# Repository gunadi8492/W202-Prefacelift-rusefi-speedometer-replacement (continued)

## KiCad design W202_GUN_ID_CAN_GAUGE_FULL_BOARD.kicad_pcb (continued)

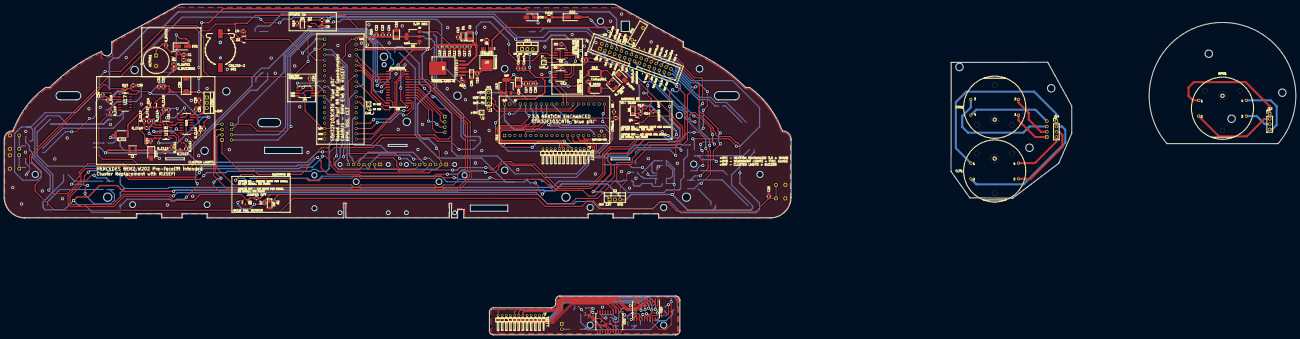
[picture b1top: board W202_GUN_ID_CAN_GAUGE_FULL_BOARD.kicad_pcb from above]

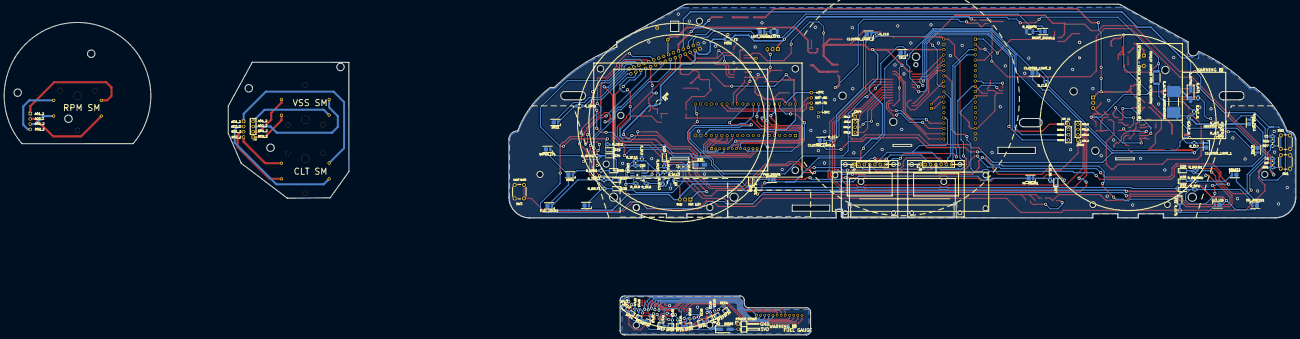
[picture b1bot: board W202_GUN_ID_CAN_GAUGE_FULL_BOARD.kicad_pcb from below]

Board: 2 copper layers, 380.0 x 103.2 mm, 236 parts (112 on the bottom side), 177 nets.

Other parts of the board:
+5VC: PinHeader_1x02_P2.00mm_Vertical
CAN_J: PinHeader_1x02_P2.00mm_Vertical
CAN_J#2: PinHeader_1x02_P2.00mm_Vertical
DIODE: 1N4007; D_SMA_Handsoldering
F3, F3#2: Polyfuse; Fuse_1206_3216Metric_Pad1.42x1.75mm_HandSolder
IGN12V JUMPER FOR ALTERNATOR: 10; R_2512_6332Metric
J3#2: VSS; PinHeader_1x04_P2.54mm_Vertical
JUMPER OPT: R_0805_2012Metric
JUMPER OPT#2: R_0805_2012Metric
POWER POINT: PinHeader_1x02_P2.54mm_Horizontal
R_WL8: 47K; R_0805_2012Metric

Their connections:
+5C: +5VC.2; also elsewhere on the board
+5VD: DIODE.1 (K), R_WL8.1; also elsewhere on the board
+5VD_S: DIODE.2 (A), POWER POINT.2
AO1_1: J3#2.1; also elsewhere on the board
AO2_1: J3#2.2; also elsewhere on the board
BO1_1: J3#2.3; also elsewhere on the board
BO2_1: J3#2.4; also elsewhere on the board
BULB_SNSR: JUMPER OPT.2; also elsewhere on the board
GND: +5VC.1, POWER POINT.1; also elsewhere on the board
HI_BEAM: JUMPER OPT#2.1; also elsewhere on the board
unnamed 69: JUMPER OPT.1; also elsewhere on the board
unnamed 70: JUMPER OPT#2.2; also elsewhere on the board
unnamed 104: R_WL8.2; also elsewhere on the board
RX CAN: CAN_J.1, CAN_J#2.1; also elsewhere on the board
TX CAN: CAN_J.2, CAN_J#2.2; also elsewhere on the board

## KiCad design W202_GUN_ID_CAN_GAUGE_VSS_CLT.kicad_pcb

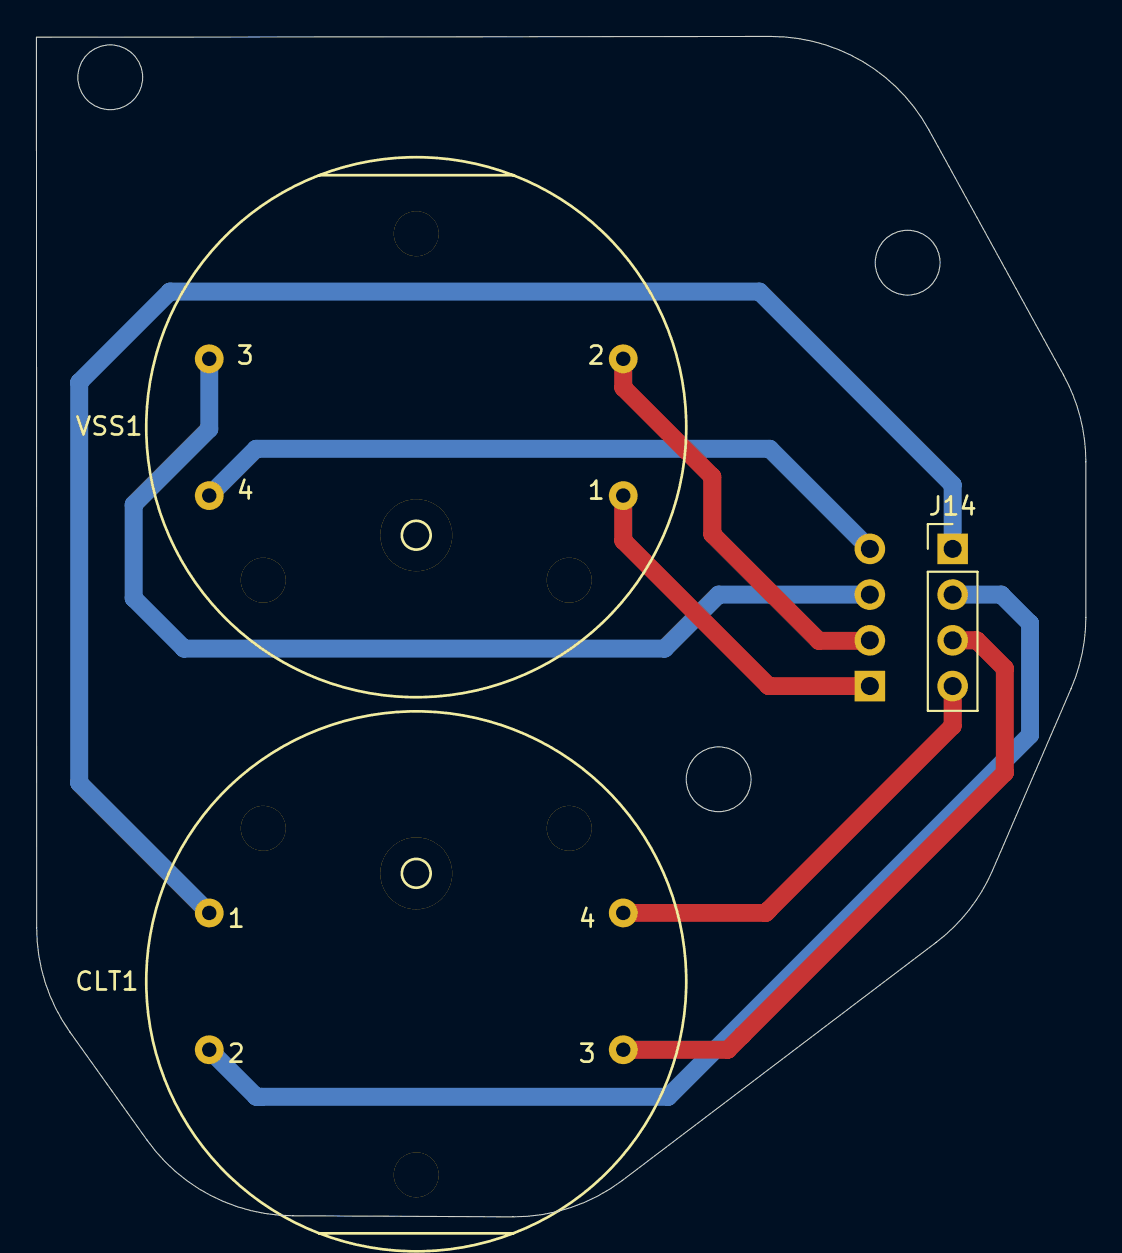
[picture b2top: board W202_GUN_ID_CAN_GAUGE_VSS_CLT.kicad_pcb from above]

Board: 2 copper layers, 58.3 x 65.6 mm, 4 parts (1 on the bottom side), 8 nets.

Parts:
CLT1: SM; X27-168__V2
J3: VSS; PinHeader_1x04_P2.54mm_Vertical
J14: CLT; PinHeader_1x04_P2.54mm_Vertical
VSS1: SM; X27-168__V2

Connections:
AO1_1: J3.1, VSS1.1
AO2_1: J3.2, VSS1.2 (-)
BO1_1: J3.3, VSS1.3
BO2_1: J3.4, VSS1.4
OUT_1C: CLT1.1, J14.1
OUT_2C: CLT1.2 (-), J14.2
OUT_3C: CLT1.4, J14.4
OUT_4C: CLT1.3, J14.3

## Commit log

2025-09-24 Initial upload
